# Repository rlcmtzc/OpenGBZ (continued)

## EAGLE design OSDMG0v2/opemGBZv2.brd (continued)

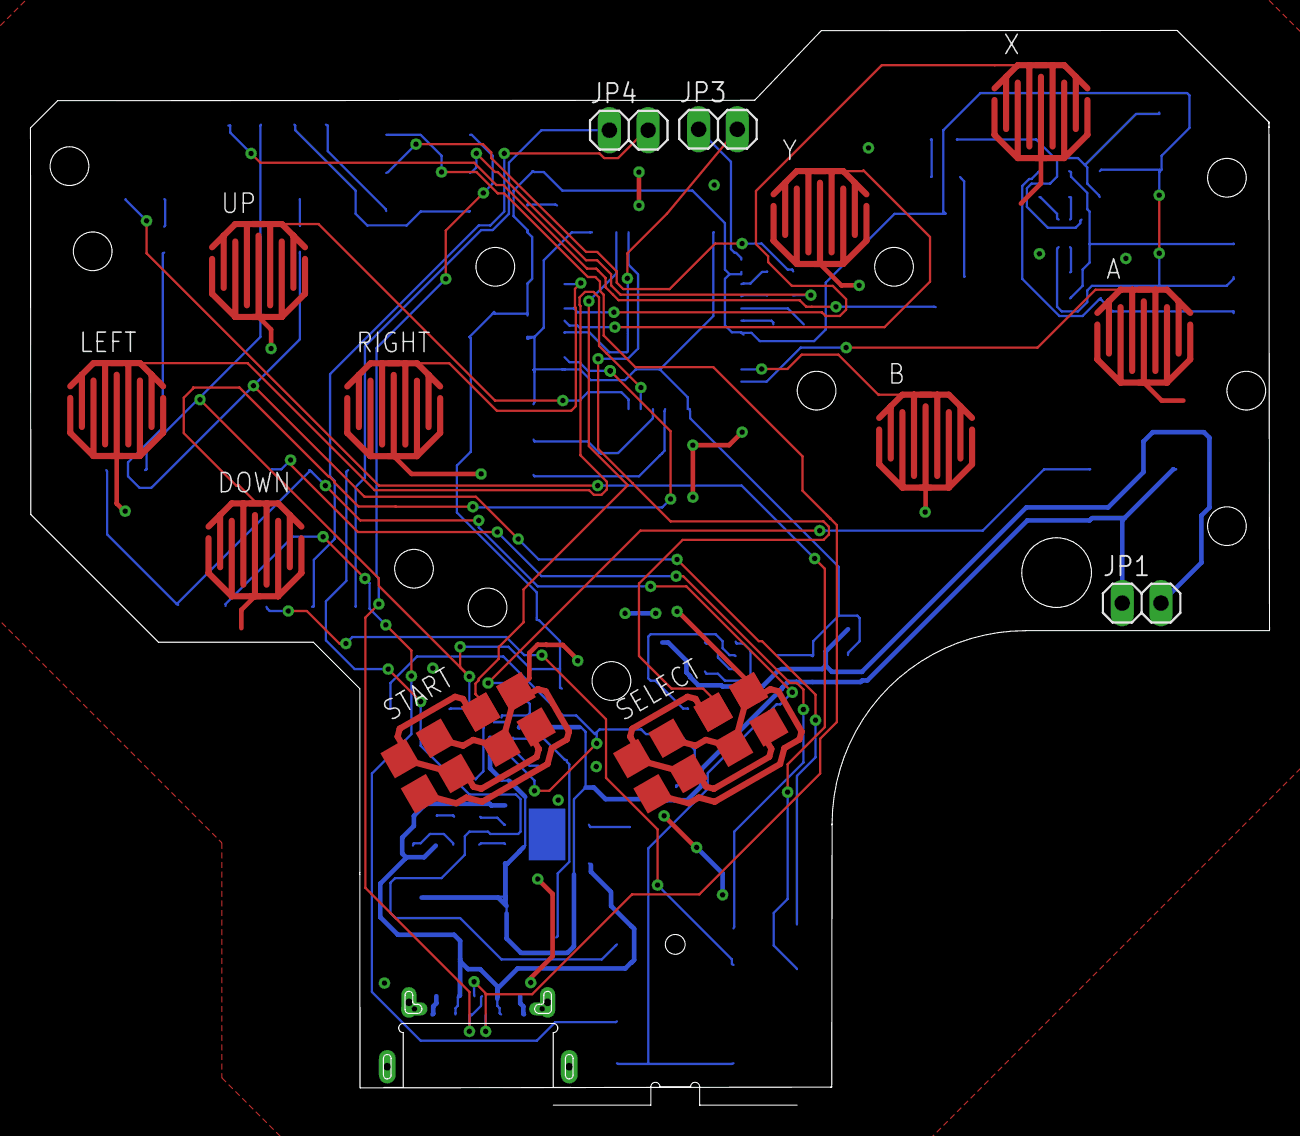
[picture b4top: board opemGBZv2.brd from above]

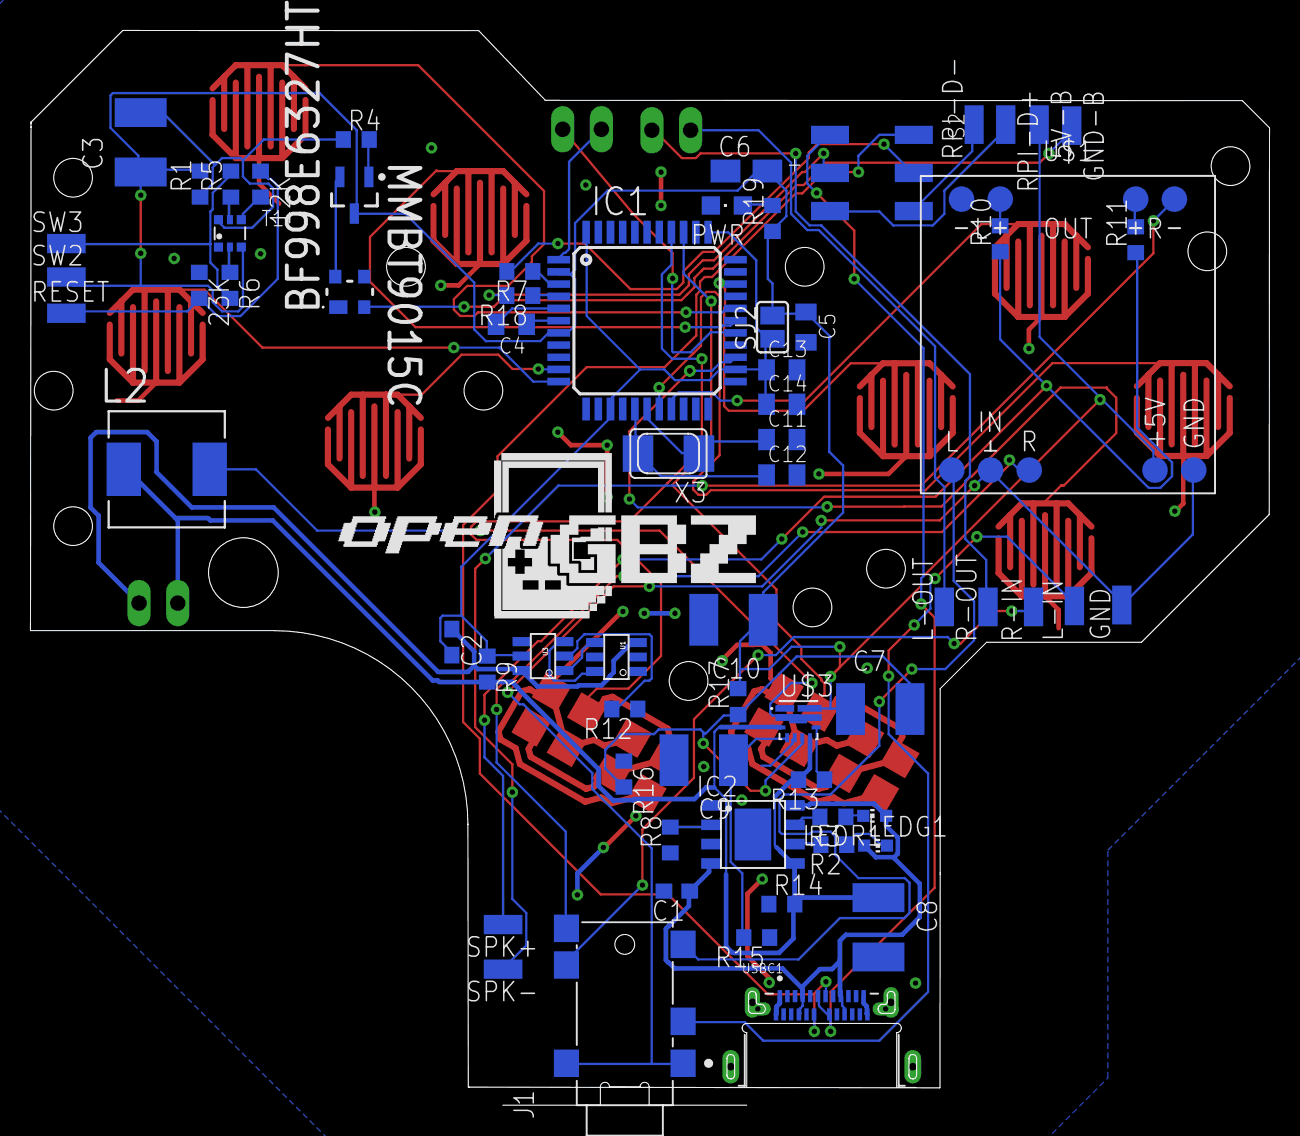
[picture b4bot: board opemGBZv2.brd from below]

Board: 2 copper layers, 81.3 x 70.5 mm, 80 parts (67 on the bottom side), 62 nets.

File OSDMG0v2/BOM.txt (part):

Bauteil         Wert               Device             Package                   Description                                                           
5V-B                               WIREPADSMD1,27-254 SMD1,27-2,54              Wire PAD connect wire on PCB                                          
12K             205k               R-EU_R0603         R0603                     RESISTOR, European symbol                                             
23K             205k               R-EU_R0603         R0603                     RESISTOR, European symbol                                             
A               DMG-BTN            DMG-BTNREGULAR     DMG-BTN                                                                                         
B               DMG-BTN            DMG-BTNREGULAR     DMG-BTN                                                                                         
BF998E6327HTSA1 INF-SOT143-4-1_V_1 INF-SOT143-4-1_V_1 INF-SOT143-4-1_V_1PRIMARY                                                                       
C1              10u                C-EUC0603          C0603                     CAPACITOR, European symbol                                            
C2              0.1uF              C-EUC0603          C0603                     CAPACITOR, European symbol                                            
C3              100uF              C-EUC1812          C1812                     CAPACITOR, European symbol                                            
C4              0.1uF              C-USC0805K         C0805K                    CAPACITOR, American symbol                                            
C5              0.1uF              C-USC0805K         C0805K                    CAPACITOR, American symbol                                            
C6              10uF               CPOL-USA/3216-18R  A/3216-18R                POLARIZED CAPACITOR, American symbol                                  
C7              10pF               C-EUC1812          C1812                     CAPACITOR, European symbol                                            
C8              10uF               C-EUC1812          C1812                     CAPACITOR, European symbol                                            
C9              10nF               C-EUC1812          C1812                     CAPACITOR, European symbol                                            
C10             33uF               C-EUC1812          C1812                     CAPACITOR, European symbol                                            
C11             18pF               C-USC0805K         C0805K                    CAPACITOR, American symbol                                            
C12             18pF               C-USC0805K         C0805K                    CAPACITOR, American symbol                                            
C13             0.1uF              C-USC0805K         C0805K                    CAPACITOR, American symbol                                            
C14             0.1uF              C-USC0805K         C0805K                    CAPACITOR, American symbol                                            
DOWN            DMG-BTN            DMG-BTNREGULAR     DMG-BTN                                                                                         
GND                                WIREPADSMD1,27-254 SMD1,27-2,54              Wire PAD connect wire on PCB                                          
GND-B                              WIREPADSMD1,27-254 SMD1,27-2,54              Wire PAD connect wire on PCB                                          
IC1             ATMEGA32U4-AU      ATMEGA32U4-AU      TQFP44                                                                                          
IC2             TP4056             TP4056             SOP-8                                                                                           
J1              SJ2-35954D-SMT-TR  SJ2-35954D-SMT-TR  CUI_SJ2-35954D-SMT-TR     4 conductors, 3.5mm, SMT Audio Jack w/ 2 Switch                       
JP1                                PINHD-1X2          1X02                      PIN HEADER                                                            
JP3                                PINHD-1X2          1X02                      PIN HEADER                                                            
JP4                                PINHD-1X2          1X02                      PIN HEADER                                                            
L-IN                               WIREPADSMD1,27-254 SMD1,27-2,54              Wire PAD connect wire on PCB                                          
L-OUT                              WIREPADSMD1,27-254 SMD1,27-2,54              Wire PAD connect wire on PCB                                          
L2              1uH                DR74-220-R         INDM7676X435N             POWER INDUCTOR                                                        
LEDG1                              LEDCHIP-LED0603    CHIP-LED0603              LED                                                                   
LEDR1                              LEDCHIP-LED0603    CHIP-LED0603              LED                                                                   
LEFT            DMG-BTN            DMG-BTNREGULAR     DMG-BTN                                                                                         
MMBT9015C       INF-SOT23_M_1      INF-SOT23_M_1      INF-SOT23_M_1PRIMARY                                                                            
PWR             GREEN              LEDCHIPLED_0805    CHIPLED_0805              LED                                                                   
R-IN                               WIREPADSMD1,27-254 SMD1,27-2,54              Wire PAD connect wire on PCB                                          
R-OUT                              WIREPADSMD1,27-254 SMD1,27-2,54              Wire PAD connect wire on PCB                                          
R1              150k               R-EU_R0603         R0603                     RESISTOR, European symbol                                             
R2              1k                 R-EU_R0603         R0603                     RESISTOR, European symbol                                             
R3              1k                 R-EU_R0603         R0603                     RESISTOR, European symbol                                             
R4              150k               R-EU_R0603         R0603                     RESISTOR, European symbol                                             
R5              1k                 R-EU_R0603         R0603                     RESISTOR, European symbol                                             
R6              1k                 R-EU_R0603         R0603                     RESISTOR, European symbol                                             
R7              22                 R-EU_R0603         R0603                     RESISTOR, European symbol                                             
R8              2k                 R-EU_R0603         R0603                     RESISTOR, European symbol                                             
R9              100                R-EU_R0603         R0603                     RESISTOR, European symbol                                             
R10             16                 R-EU_R0603         R0603                     RESISTOR, European symbol                                             
R11             16                 R-EU_R0603         R0603                     RESISTOR, European symbol                                             
R12             2k                 R-EU_R0603         R0603                     RESISTOR, European symbol                                             
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
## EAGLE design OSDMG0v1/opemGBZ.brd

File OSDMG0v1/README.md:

# First Version of my opensource DMG Board

**Author:** rlcmtzc12 *(Based on rlcmtzc12 design)*  
**Tested:** Yes and working  
**BOM-file:** Included  
**Build:** [Build](https://www.sudomod.com/forum/viewtopic.php?f=43&t=6388)

## Description:

This board has an integrated charging and Boost circuit. The Boost circuit is based on the MT3608 step up IC. (Datasheed found [here](https://www.olimex.com/Products/Breadboarding/BB-PWR-3608/resources/MT3608.pdf)) The outputvoltage is set to around 5.2 Volt. The Boost circuit can be switched on with a powerswitch. I have tested the boostcitcuit with 1,4 A which works fine but the IC gets a little bit warm. I also tested it with 2A which is the max outputcurrent from the Datasheed which works but the IC get really warm so I wouldnd suggest that. On 1 - 1,2A the IC isn´t even warm so it works perfectly fine in this range. The charging circuit of the Battery is based on TP4056 IC which can charge a single lithium-ion battery with up to 1A (Datasheed found [here](https://www.e-gizmo.net/oc/kits%20documents/TP4056-1A%20Li-ion%20Battery%20Charger/TP4056-1A%20Li-ion%20battery%20charger%20Manual.pdf)). Also I integrated the FS312G-F IC which protect the Battery from overcharge, overdischarge and overcurrent (Datasheed found [here](https://www.ic-fortune.com/upload/Download/FS312F-G-DS-12_EN.pdf)). The board will be charged with an usb type c connector. On the board is place for an standard PAM module which then connect to place for a volumewheel and the aux-port. On the front there are the standard buttons (Up, Down, Left, Right, Start, Select, A, B, X, Y)  

## Get Project:
[Here](https://easyeda.com/editor#id=|1b6bda1489604f5b8086fe82ce4b43ba|fd54b8f932f541aa9ddfa8aae15e51a3) you can edit and change the Project online. There are also the Altium and Eagle files.
## Images:

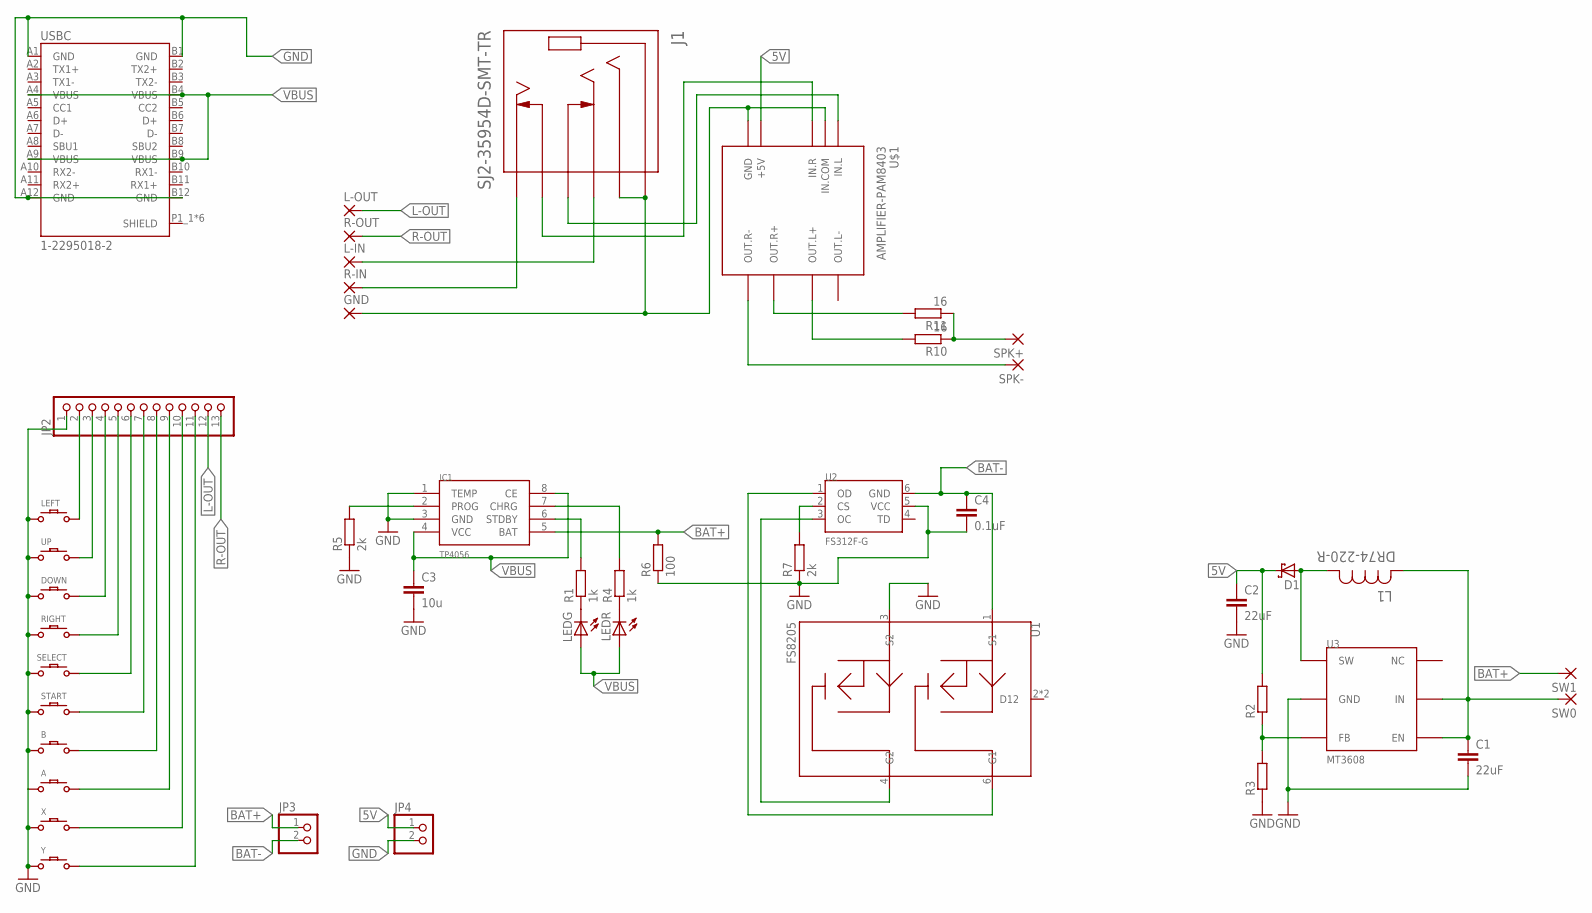
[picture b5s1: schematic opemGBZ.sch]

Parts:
A: DMG-BTN
B: DMG-BTN
C1, C2: 22uF; C1812
C3: 10u; C0603
C4: 0.1uF; C0603
D1: SCHOTTKY-DIODESMD; SMB
DOWN: DMG-BTN
GND: WIREPADSMD1,27-254; SMD1,27-2,54
IC1: TP4056; SOP-8
J1: SJ2-35954D-SMT-TR; CUI_SJ2-35954D-SMT-TR
JP2: PINHD-1X13; 1X13
JP3, JP4: PINHD-1X2; 1X02
L1: DR74-220-R; INDM7676X435N
L-IN: WIREPADSMD1,27-254; SMD1,27-2,54
L-OUT: WIREPADSMD1,27-254; SMD1,27-2,54
LEDG: LEDCHIP-LED0603; CHIP-LED0603
LEDR: LEDCHIP-LED0603; CHIP-LED0603
LEFT: DMG-BTN
R1, R4: 1k; R0603
R2, R3: R-EU_R0603; R0603
R5, R7: 2k; R0603
R6: 100; R0603
R10, R11: 16; R0603
R-IN: WIREPADSMD1,27-254; SMD1,27-2,54
R-OUT: WIREPADSMD1,27-254; SMD1,27-2,54
RIGHT: DMG-BTN
SELECT: DMG-BTN; DMG-SEL
SPK+: WIREPADSMD1,27-254; SMD1,27-2,54
SPK-: WIREPADSMD1,27-254; SMD1,27-2,54
START: DMG-BTN; DMG-SEL
SW0, SW1: WIREPADSMD1,27-254; SMD1,27-2,54
U1: FS8205; SOT23-6
U2: FS312F-G; SOT23-6
U3: MT3608; SOT23-6
U$1: AMPLIFIER-PAM8403
UP: DMG-BTN
USBC: 1-2295018-2; TE_1-2295018-2
X: DMG-BTN
Y: DMG-BTN

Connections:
5V: C2.1, D1.C, JP4.1, R2.2, U$1.+5V
BAT+: C1.1, IC1.5 (BAT), L1.2, R6.2, SW1.1, U3.4 (EN), U3.5 (IN)
BAT-: C4.1, U1.1 (S1), U2.6 (GND)
L-OUT: JP2.12, L-OUT.1
L-OUT1: SW0.1
unnamed: JP2.2, LEFT.P$2
unnamed: JP2.3, UP.P$2
unnamed: DOWN.P$2, JP2.4
unnamed: JP2.5, RIGHT.P$2
unnamed: JP2.6, SELECT.P$1
unnamed: JP2.7, START.P$1
unnamed: B.P$2, JP2.8
unnamed: A.P$2, JP2.9
unnamed: JP2.10, X.P$2
unnamed: JP2.11, Y.P$2
unnamed: IC1.6 (STDBY), R1.2
unnamed: IC1.7 (CHRG), R4.2
unnamed: LEDG.C, R1.1
unnamed: LEDR.C, R4.1
unnamed: IC1.2 (PROG), R5.2
unnamed: U1.4 (G2), U2.3 (OC)
unnamed: U1.6 (G1), U2.1 (OD)
unnamed: R7.2, U2.2 (CS)
unnamed: D1.A, L1.1, U3.1 (SW)
unnamed: R2.1, R3.2, U3.3 (FB)
unnamed: R11.2, U$1.OUT.R+
unnamed: GND.1, J1.1 (SLEEVE), J1.4 (RING2), U$1.GND, U$1.IN.COM
unnamed: J1.11 (RING1_SWITCH), U$1.IN.L
unnamed: J1.10 (TIP_SWITCH), U$1.IN.R
unnamed: J1.2 (TIP), R-IN.1
unnamed: J1.3 (RING1), L-IN.1
unnamed: R10.2, U$1.OUT.L+
unnamed: R10.1, R11.1, SPK+.1
unnamed: SPK-.1, U$1.OUT.R-
R-OUT: JP2.13, R-OUT.1
VBUS: C3.1, IC1.4 (VCC), IC1.8 (CE), LEDG.A, LEDR.A, USBC.A4 (VBUS), USBC.A9 (VBUS), USBC.B4 (VBUS), USBC.B9 (VBUS)

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
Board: 2 copper layers, 46 parts (0 on the bottom side), 37 nets, no tracks yet.

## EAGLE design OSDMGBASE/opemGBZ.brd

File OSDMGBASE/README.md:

# Base Version of my opensource DMG Board

**Author:** rlcmtzc12 *(Based on rlcmtzc12 design)*  
**Tested:** yes  
**BOM-file:** not needed   
**Build:** /  

## Description:

This is the Base Project. The other Projhects I made are based on this one. It only includes a normal button PCB with a common ground and the normal dimensions of the gameboy. This is a good startingpoint for all other projects.

## Get Project:
The attached Eagle-files include everything.

## Images:

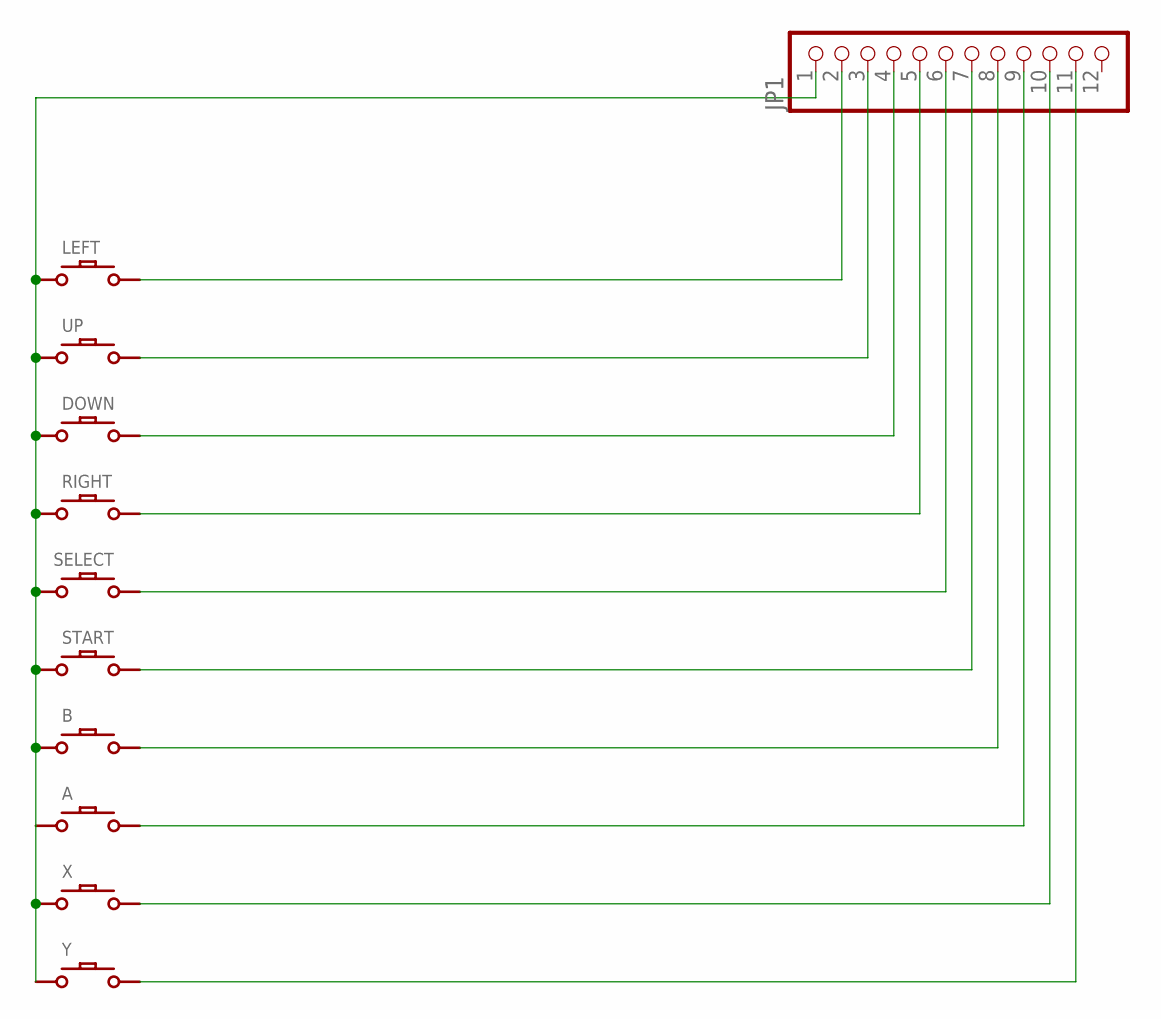
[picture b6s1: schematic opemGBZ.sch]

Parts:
A: DMG-BTN
B: DMG-BTN
DOWN: DMG-BTN
JP1: PINHD-1X12; 1X12
LEFT: DMG-BTN
RIGHT: DMG-BTN
SELECT: DMG-BTN; DMG-SEL
START: DMG-BTN; DMG-SEL
UP: DMG-BTN
X: DMG-BTN
Y: DMG-BTN

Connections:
GND: A.P$1, B.P$1, DOWN.P$1, JP1.1, LEFT.P$1, RIGHT.P$1, SELECT.P$2, START.P$2, UP.P$1, X.P$1, Y.P$1
unnamed: JP1.2, LEFT.P$2
unnamed: JP1.3, UP.P$2
unnamed: DOWN.P$2, JP1.4
unnamed: JP1.5, RIGHT.P$2
unnamed: JP1.6, SELECT.P$1
unnamed: JP1.7, START.P$1
unnamed: B.P$2, JP1.8
unnamed: A.P$2, JP1.9
unnamed: JP1.10, X.P$2
unnamed: JP1.11, Y.P$2

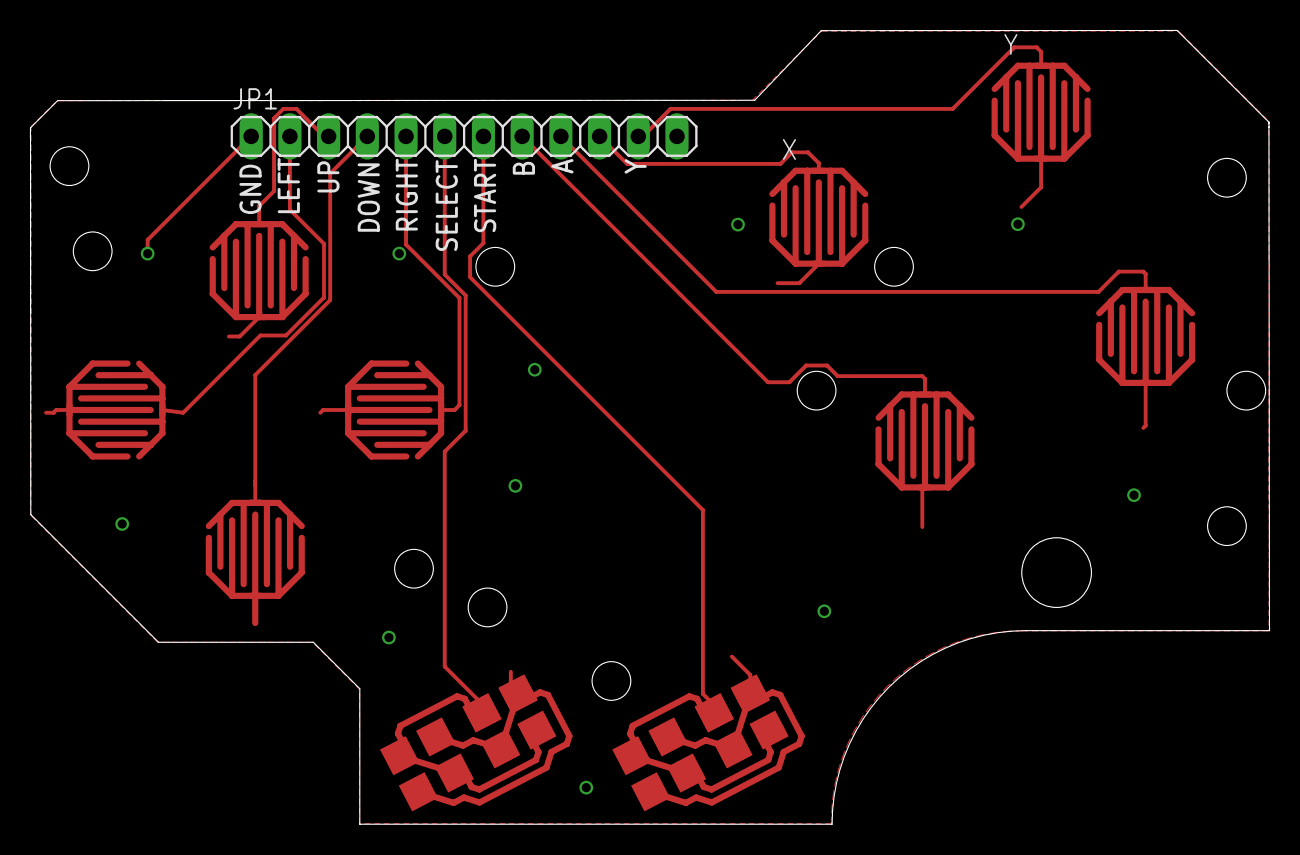
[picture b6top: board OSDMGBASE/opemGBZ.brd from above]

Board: 2 copper layers, 81.3 x 52.1 mm, 11 parts (0 on the bottom side), 11 nets.

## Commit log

2018-08-24 rename
2018-08-24 logos
2018-08-24 base open gbz
2018-08-24 structure
2018-08-25 Eagle files brd not routed yet
2018-08-25 update Eagle
2018-08-30 new boost circuit
2018-08-31 update board
2018-09-01 everything routed up GND
2018-09-04 Eagle finished
2018-09-04 update and finish all projects
2018-09-04 Bom file
2018-12-23 Add files via upload
    Error fix
2019-01-25 Adding GBP Base
2019-01-25 Update Readme.md v2
2019-01-26 update new project
    update new project
2019-01-28 Second Revision
    - NEW Buttons
    - NEW Design
2019-01-29 Second Revision
2019-01-29 Minor Changes
2019-01-31 update board
    5V and GND Pads and better placement of the leonardo
2019-03-02 Drill FIX
2019-03-02 Revision 2 Minor Fixes
2019-03-03 Release V2
2021-02-08 Update README.md
    Add License
2021-02-08 Create LICENSE.md
    Add License
